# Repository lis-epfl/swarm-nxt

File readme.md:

# SwarmNxt

A system to setup and manage drones for swarming research, with [OmniNxt](https://github.com/HKUST-Aerial-Robotics/OmniNxt) hardware (Liu et. al.). The hardware and software setup tutorial can be found here [https://lis-epfl.github.io/swarm-nxt/](https://lis-epfl.github.io/swarm-nxt/).

The full video can be watched at [https://youtu.be/9aOr5EDLQEo](https://youtu.be/9aOr5EDLQEo).

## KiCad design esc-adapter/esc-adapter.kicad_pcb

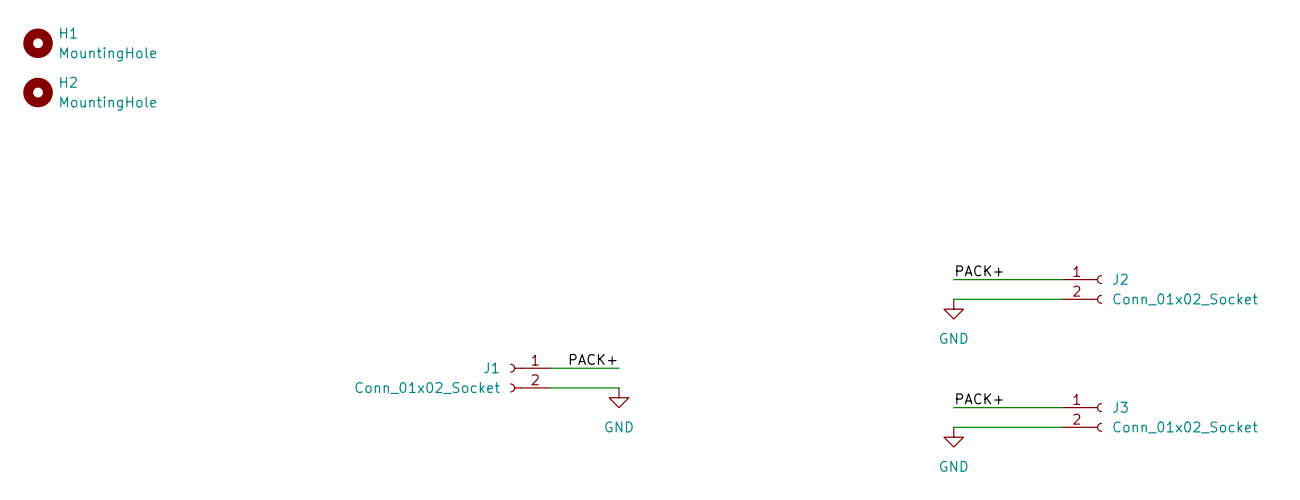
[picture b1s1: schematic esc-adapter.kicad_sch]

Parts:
H1, H2: MountingHole; MountingHole_2.2mm_M2
J1: Conn_01x02_Socket; ESCConnection
J2, J3: Conn_01x02_Socket; BatteryConnection

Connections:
/PACK+: J1.1, J2.1, J3.1
GND: J1.2, J2.2, J3.2

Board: 2 copper layers, 5 parts (0 on the bottom side), 2 nets, no tracks yet.

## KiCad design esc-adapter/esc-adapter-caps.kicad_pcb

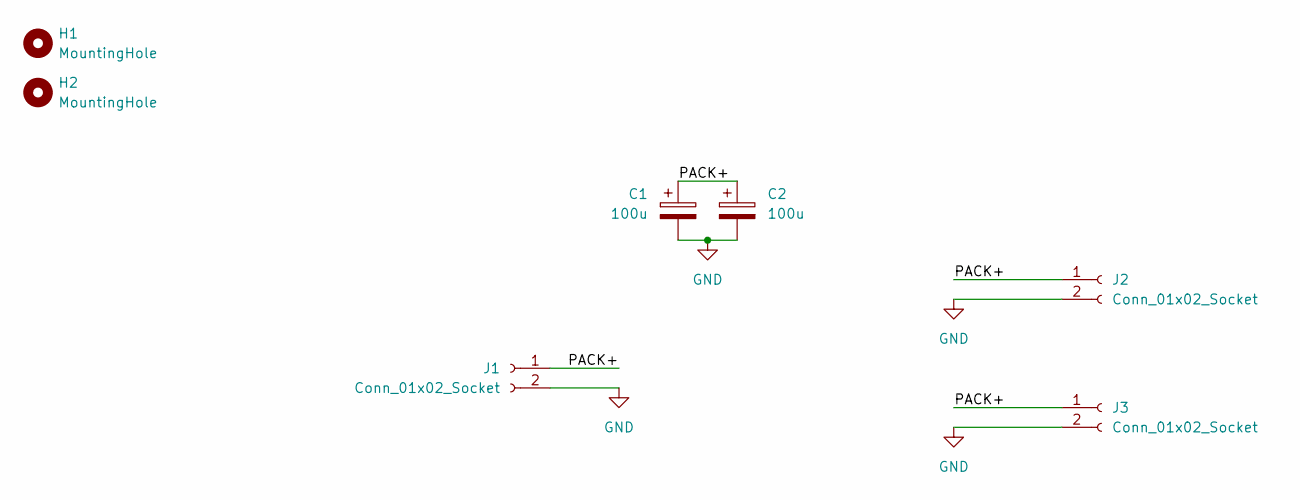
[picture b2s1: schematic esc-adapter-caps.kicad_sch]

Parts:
C1: 100u; MINIIMAL_CP_Radial_D6.3mm_P2.50mm; PartNumber ESL107M035AE3AA
C2: 100u; MINIIMAL_CP_Radial_D6.3mm_P2.50mm
H1, H2: MountingHole; MountingHole_2.2mm_M2
J1: Conn_01x02_Socket; ESCConnection
J2, J3: Conn_01x02_Socket; BatteryConnection

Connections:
/PACK+: C1.1, C2.1, J1.1, J2.1, J3.1
GND: C1.2, C2.2, J1.2, J2.2, J3.2

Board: 2 copper layers, 7 parts (0 on the bottom side), 2 nets, no tracks yet.

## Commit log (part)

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2025-08-29 dsm: whats going on
2025-08-29 fix annoying python issues
2025-08-29 fix host computer stuff
2025-09-04 easier shutdown
2025-09-04 set params
2025-09-04 some more changes for param update
2025-09-04 compress bags
2025-09-04 fix ensure params lco
2025-09-05 fix peer list path
2025-09-05 fix default path for peers
2025-09-05 Initial plan
2025-09-05 Add MAVLink log collection script and integrate into postflight
2025-09-05 Add documentation for MAVLink log collection and postflight procedures
2025-09-05 set px4 time on boot
2025-09-05 start scripts
2025-09-10 update inv
2025-09-11 somechanges
2025-09-11 Merge
2025-09-11 remove trailing / in etc
2025-09-11 ensure_params: whole loop
2025-09-11 add mav sys id
2025-09-11 update controller for time based
2025-09-11 tweaks
2025-09-11 print goals
2025-09-11 position
2025-09-11 switch to best effort
2025-09-11 fix uninit req
2025-09-11 remove deprecated traj check
2025-09-11 add dtail print
2025-09-11 print after scaling
2025-09-11 print offset
2025-09-11 fix signbit bug
2025-09-11 log properly
2025-09-11 fix clock check
2025-09-11 add setpoint pos
2025-09-11 fix traj
2025-09-11 add plugins
2025-09-11 speed up
2025-09-11 update bounds eg
2025-09-11 check alt
2025-09-12 fix controller enable
2025-09-12 send controller enable msgs
2025-09-12 set height
2025-09-12 setup: limit to one reboot
2025-09-12 add build image
2025-09-12 install camera things
2025-09-12 reenable reboot
2025-09-12 install gurobi
2025-09-12 download and build hdsm package
2025-09-13 some tweaks to build properly
2025-09-13 ctrl: log more frequently
2025-09-13 lookahead 100ms
2025-09-13 tweaks for stability?
2025-09-13 reduce lookahead
2025-09-13 integrate hdsm in ctrl
2025-09-13 add to launch file
2025-09-13 use int for drone num
2025-09-13 remove simple planner
2025-09-13 tweak drone launch
2025-09-13 no need to sub1!
2025-09-13 add gurobi stuff to start script
2025-09-13 attempt to setup host computer properly
2025-09-13 send traj/traj_full to host comp
2025-09-13 more broader broadcasting of traj_full
2025-09-13 hdsm: frames
2025-09-13 local build task
2025-09-13 frame_id consolidation
2025-09-13 rob_id -> id
2025-09-14 planner map
2025-09-14 forward service
2025-09-14 start planning service in gui!
2025-09-14 remove old traj from bridge
2025-09-14 update to yaml, add agent name to gui
2025-09-14 remove whitespace
2025-09-14 send build scripts instead of direct commands
2025-09-14 there were two gui scripts??
2025-09-14 fix plannign service name
2025-09-14 move service bridge
2025-09-14 invert service direction
2025-09-14 planner start: switch from srv to msg
2025-09-14 intize dronenum
2025-09-14 fix topic name
2025-09-14 fix qos
2025-09-14 make it executable
2025-09-14 smlink install
2025-09-14 improve ansible update docs
2025-09-14 remove reached destination logic
2025-09-14 start at i = 1 for dt
2025-09-14 add safety flag to mode change
2025-09-14 store traj_full
2025-09-14 Fix card bouncing effect in drone GUI by removing transform hover animation
2025-09-14 mcap everything from the planner
2025-09-14 reset send rate on landing
2025-09-14 speed up controller
2025-09-14 stop daemon before launch
2025-09-17 demote chatty prints to debug
2025-09-17 simple goal giver
2025-09-17 link host computer stuff properly
2025-09-17 reorder multiagent planner
2025-09-17 oops
2025-09-17 deconflict
2025-09-17 correct point access
2025-09-17 make z float
2025-09-17 lower limit for detection of takeoff
2025-09-17 increase vempty
2025-09-17 swap position command
2025-09-17 star tplan w ctrl
2025-09-18 error out when nothign found
2025-09-19 fw update
2025-09-23 update optitrack master
2025-09-23 fix fw name
2025-09-23 send tfs to all drones
2025-10-03 ensure ros off
2025-10-03 add px4 msgs submodule
2025-10-03 format
2025-10-05 remove px4 msgs
2025-10-05 add px4_msgs to drone planner
2025-10-05 eigen include
2025-10-05 fix compile errors
    Squashed commit of the following:
    commit 488fef98388112870ab9287424d8df981dfc48a2
    Author: Niel Mistry <niel@nielmistry.com>
    Date: Sun Oct 5 21:57:16 2025 +0200
    suspend ensure params
    commit ef43daa376bab4c3a1f9fa9e544b6d17d982f098
2025-10-05 fix container build
2025-10-05 fix versions
2025-10-06 allow downgrades for docker and apt install
2025-10-06 remove time set
2025-10-06 clone px4 packages
2025-10-06 add xrce agent and remove mavros
2025-10-06 transition xrce to its own service
2025-10-06 remove hold mode
2025-10-06 remove ns from drone launch
2025-10-06 add fmu to rosbag (consequence of crash)
    https://docs.google.com/document/d/1EqBbX9S9wBg_GelVs3_Od1xccYq82JXtlJOanYNnhJw/edit?usp=sharing
2025-10-26 update launch file for the drones
2025-10-28 udpate
2025-11-07 update safety checker
2025-11-10 add thrust topic in config
2025-11-10 only publish torque and thrust commands when we are already in offboard
2025-11-11 update drone state manager
2025-11-11 fix target_system
2025-11-13 add different initial goals for multiple drones
2025-11-15 updage
2025-11-20 add microxrce
2025-11-20 add shutdown ansible
2025-12-03 fix docker install problem
2025-12-03 clarify flashing docs for sdk
2025-12-05 add clock limit to avoid big current swings that crash the damiao board
2025-12-08 update docs
2025-12-09 update threshold for focus
2025-12-10 add timings
2025-12-15 update server address
2025-12-17 update safety flag print out
2025-12-20 add priority
2026-01-27 fix bullet points
2026-01-27 checkout submodules for ros build check
2026-01-27 remove mavros dependency from drone_state_manager
2026-01-27 Deployed fa0d3c4 with MkDocs version: 1.6.1
2026-01-28 fix ros workflow
2026-01-28 add multi_agent_msgs to workflow
2026-01-28 remove vscode settings
2026-01-28 add px4_ros_com to workflow
2026-02-01 update docs with image
2026-02-01 remove manual setup
2026-02-01 fix typo
2026-02-02 add video
2026-02-03 update hdsm source
2026-02-04 add assembly video link
2026-02-10 add clock sync between px4 and ros2
2026-02-10 remove clock sync between px4 and ros2 since the offset is continuously updated with synct = 1
2026-02-14 update gurobit
2026-02-14 update commands
2026-04-24 update planner branch
2026-04-24 update gurobi path
2026-04-25 add enable_cameras and enable_depth instead of enable_vision
2026-04-25 Deployed c7d60ce with MkDocs version: 1.6.1
